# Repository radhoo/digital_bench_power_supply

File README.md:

# digital_bench_power_supply
A new design for a digital bench power supply built using the Atmega8.

(C) 2015 Radu Motisan, http://www.pocketmagic.net/digital-bench-power-supply/
radu.motisan@gmail.com

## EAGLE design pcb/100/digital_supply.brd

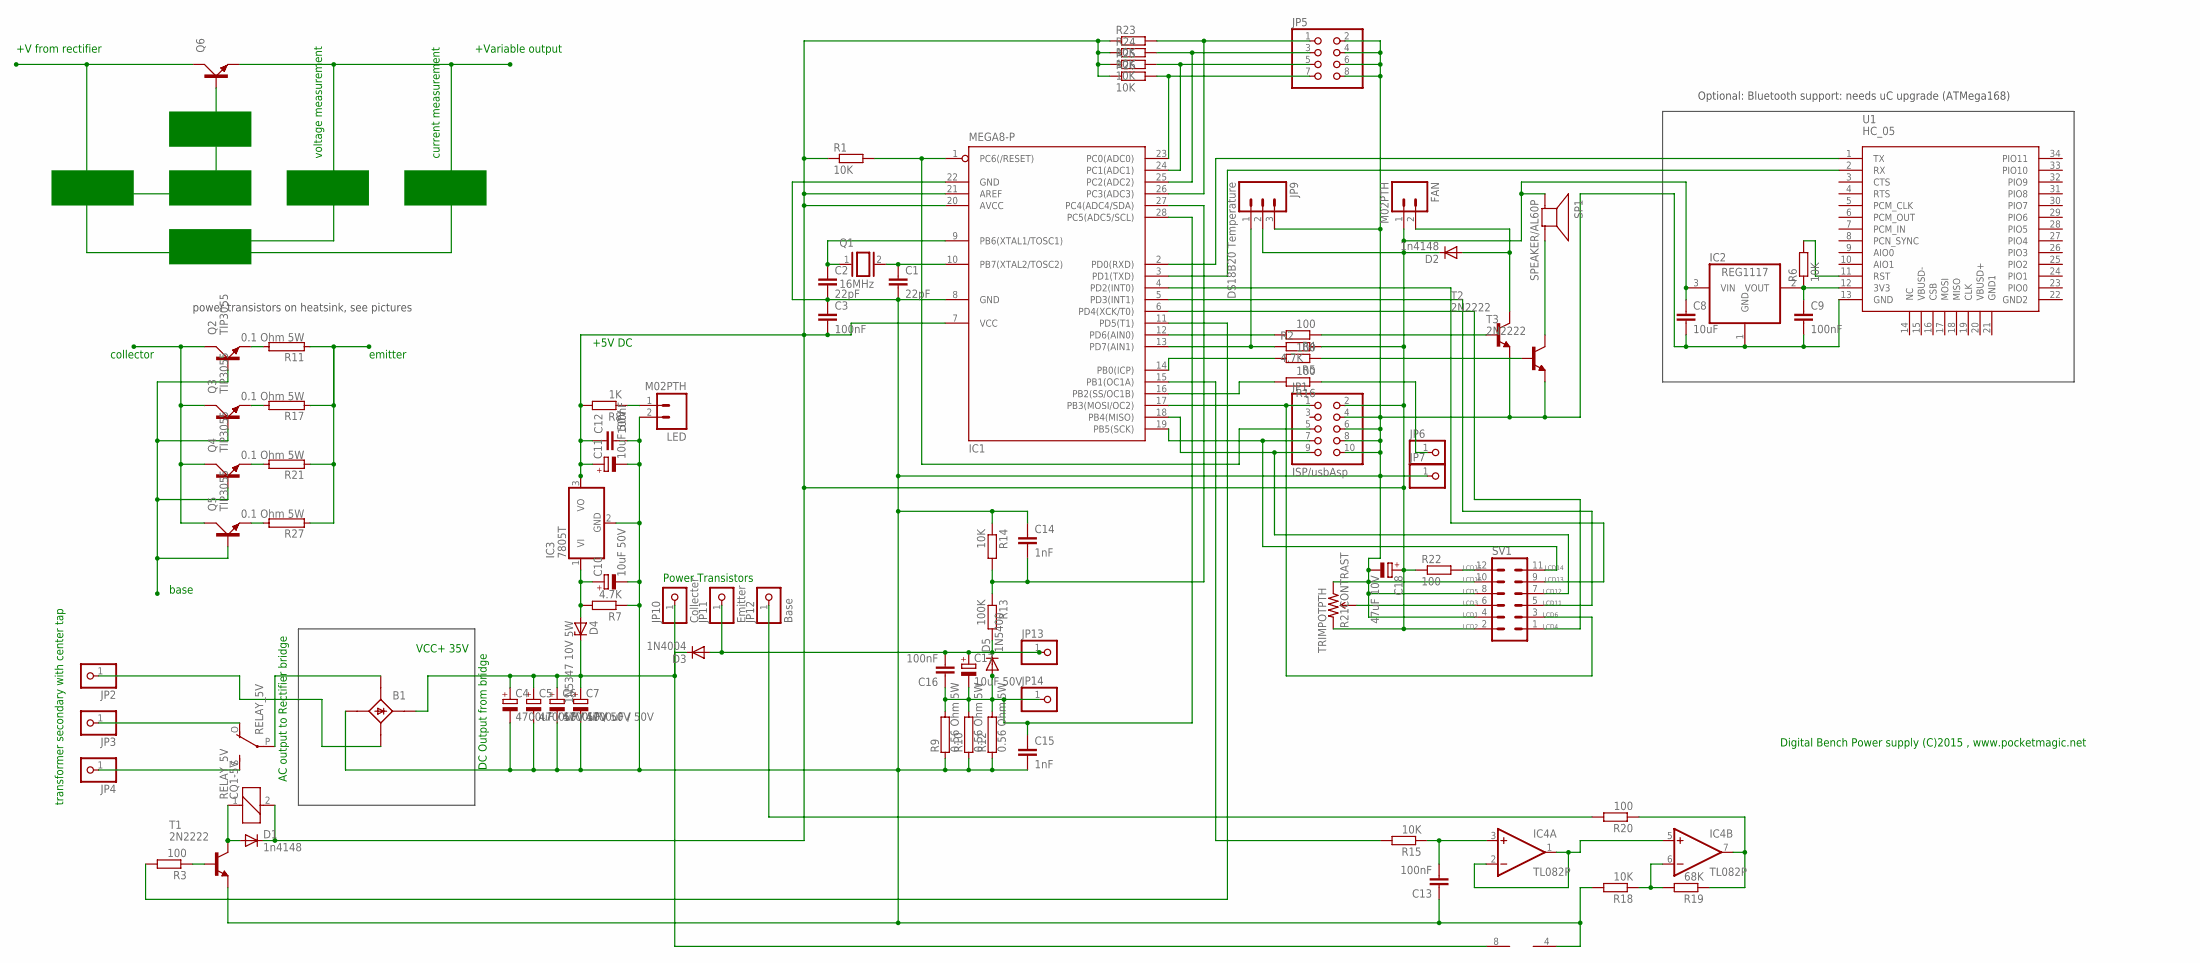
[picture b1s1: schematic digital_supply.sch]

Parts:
B1: B25A-
C1, C2: 22pF; C025-024X044
C3, C12, C13, C16: 100nF; C025-024X044
C4, C5, C6, C7: 4700uF / 50V; E7,5-18
C8: 10uF; C0805
C9: 100nF; C0805
C10, C11, C17: 10uF 50V; E2-5
C14, C15: 1nF; C025-024X044
C18: 47uF 10V; E2-5
D1, D2: 1n4148; D-5
D3: 1N4004; DO41-10
D4: 1N5347 10V 5W; DO34Z7
D5: 1N5400; DO201-15
FAN: M02PTH; 1X02
IC1: MEGA8-P; DIL28-3
IC2: REG1117; SOT223
IC3: 7805T; TO220H
IC4: TL082P; DIL08
JP1: ISP/usbAsp; 2X05
JP2, JP3, JP4, JP6, JP7, JP13, JP14: PINHD-1X1; 1X01
JP5: PINHD-2X4; 2X04
JP9: DS18B20 Temperature; 1X03
JP10: Collecter; 1X01
JP11: Emitter; 1X01
JP12: Base; 1X01
LED: M02PTH; 1X02
Q1: 16MHz; QS
Q2, Q3, Q4, Q5, Q6: TIP3055; TOP3AV
R1, R14, R15, R18, R23, R24, R25, R26: 10K; 0204/7
R2, R7: 4.7K; 0204/7
R3, R4, R5, R16, R20, R22: 100; 0204/7
R6: 10K; M0805
R8: 1K; 0204/7
R9, R10, R12: 0.56 Ohm 5W; AC05
R11, R17, R21, R27: 0.1 Ohm 5W; AC05
R13: 100K; 0204/7
R19: 68K; 0204/7
R21CONTRAST: TRIMPOTPTH; TRIM_POT_PTH
RELAY_5V: CQ1-5V; G5LE
SP1: SPEAKER/AL60P; AL60P
SV1: MA06-2
T1, T2, T3: 2N2222; TO92-EBC-OVAL
U1: HC_05; BLUETOOTH_SMD

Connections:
unnamed: C1.1, IC1.10 (PB7(XTAL2/TOSC2)), Q1.2
unnamed: C2.1, IC1.9 (PB6(XTAL1/TOSC1)), Q1.1
unnamed: B1.-1 (-), C1.2, C2.2, C3.1, C4.-, C5.-, C6.-, C7.-, C8.2, C9.2, C10.-, C11.-, C12.2, C13.1, C14.1, C15.2, C18.-, IC1.8 (GND), IC1.22 (GND), IC2.1 (GND), IC3.2 (GND), IC4.4 (V-), JP1.4, JP1.6, JP1.8, JP1.10, JP5.2, JP5.4, JP5.6, JP5.8, JP7.1, JP9.3, LED.2, R7.1, R9.1, R10.1, R12.1, R14.1, R18.2, R21CONTRAST.1 (CCW), SV1.4, SV1.8, SV1.10, T1.E, T2.E, T3.E, U1.13 (GND)
unnamed: LED.1, R8.1
unnamed: IC1.1 (PC6(/RESET)), JP1.5, R1.2
unnamed: IC1.17 (PB3(MOSI/OC2)), JP1.1, SV1.3
unnamed: IC1.18 (PB4(MISO)), JP1.9, SV1.7
unnamed: IC1.4 (PD2(INT0)), SV1.9
unnamed: IC1.14 (PB0(ICP)), R5.2
unnamed: IC1.13 (PD7(AIN1)), JP9.1, R2.1
unnamed: JP3.1, RELAY_5V.O
unnamed: JP4.1, RELAY_5V.S
unnamed: B1.AC2- (AC2), JP2.1
unnamed: B1.AC1- (AC1), RELAY_5V.P
unnamed: D1.A, RELAY_5V.1, T1.C
unnamed: B1.+1 (+), C4.+, C5.+, C6.+, C7.+, D3.C, D4.C, IC4.8 (V+), JP10.1
unnamed: R3.1, T1.B
unnamed: IC1.11 (PD5(T1)), R3.2
unnamed: IC1.12 (PD6(AIN0)), R4.2
unnamed: C15.1, C16.1, C17.-, D5.A, IC1.28 (PC5(ADC5/SCL)), JP14.1, R9.2, R10.2, R12.2
unnamed: IC1.15 (PB1(OC1A)), R15.2
unnamed: C14.2, IC1.27 (PC4(ADC4/SDA)), R13.1, R14.2
unnamed: R4.1, T2.B
unnamed: D2.A, FAN.2, T2.C
unnamed: IC1.16 (PB2(SS/OC1B)), R16.2
unnamed: R5.1, T3.B
unnamed: SP1.2 (-), T3.C
unnamed: C16.2, C17.+, D3.A, D5.C, JP11.1, JP13.1, R13.2
unnamed: IC1.2 (PD0(RXD)), U1.1 (TX)
unnamed: IC1.3 (PD1(TXD)), U1.2 (RX)
unnamed: C9.1, IC2.2 (VOUT), R6.1, U1.12 (3V3)
unnamed: C10.+, D4.A, IC3.1 (VI), R7.2
unnamed: R6.2, U1.11 (RST)
unnamed: Q2.E, R11.2
unnamed: JP6.1, R16.1
unnamed: C13.2, IC4.3 (+IN), R15.1
unnamed: IC4.1 (OUT), IC4.2 (-IN), IC4.5 (+IN)
unnamed: IC4.6 (-IN), R18.1, R19.2
unnamed: IC4.7 (OUT), R19.1, R20.1
unnamed: JP12.1, R20.2
unnamed: IC1.6 (PD4(XCK/T0)), SV1.1
unnamed: IC1.5 (PD3(INT1)), SV1.5
unnamed: IC1.19 (PB5(SCK)), JP1.7, SV1.11
unnamed: R21CONTRAST.2 (WIPER), SV1.6
unnamed: R22.2, SV1.12
unnamed: C3.2, C8.1, C11.+, C12.1, C18.+, D1.C, D2.C, FAN.1, IC1.7 (VCC), IC1.20 (AVCC), IC1.21 (AREF), IC2.3 (VIN), IC3.3 (VO), JP1.2, JP9.2, R1.1, R2.2, R8.2, R21CONTRAST.3 (CW), R22.1, R23.1, R24.1, R25.1, R26.1, RELAY_5V.2, SP1.1 (+), SV1.2
unnamed: IC1.26 (PC3(ADC3)), JP5.1, R23.2
unnamed: IC1.25 (PC2(ADC2)), JP5.3, R24.2
unnamed: IC1.24 (PC1(ADC1)), JP5.5, R25.2
unnamed: IC1.23 (PC0(ADC0)), JP5.7, R26.2
unnamed: Q3.E, R17.2
unnamed: Q4.E, R21.2
unnamed: Q5.E, R27.2
unnamed: R11.1, R17.1, R21.1, R27.1
unnamed: Q2.C, Q3.C, Q4.C, Q5.C
unnamed: Q2.B, Q3.B, Q4.B, Q5.B

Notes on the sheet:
transformer secondary with center tap
AC output to Rectifier bridge
DC Output from bridge
VCC+ 35V
+5V DC
Power Transistors
Optional: Bluetooth support: needs uC upgrade (ATMega168)
LCD2 LCD4
LCD1 LCD6
LCD3 LCD11
LCD5 LCD12
LCD16 LCD13
LCD15 LCD14
power transistors on heatsink, see pictures
base
emitter
collector
control logic
+V from rectifier
DAC
ADC
AMPLIFIER
atmega8
SHUNT
+Variable output
voltage measurement
current measurement
DIVIDER
Digital Bench Power supply (C)2015 , www.pocketmagic.net

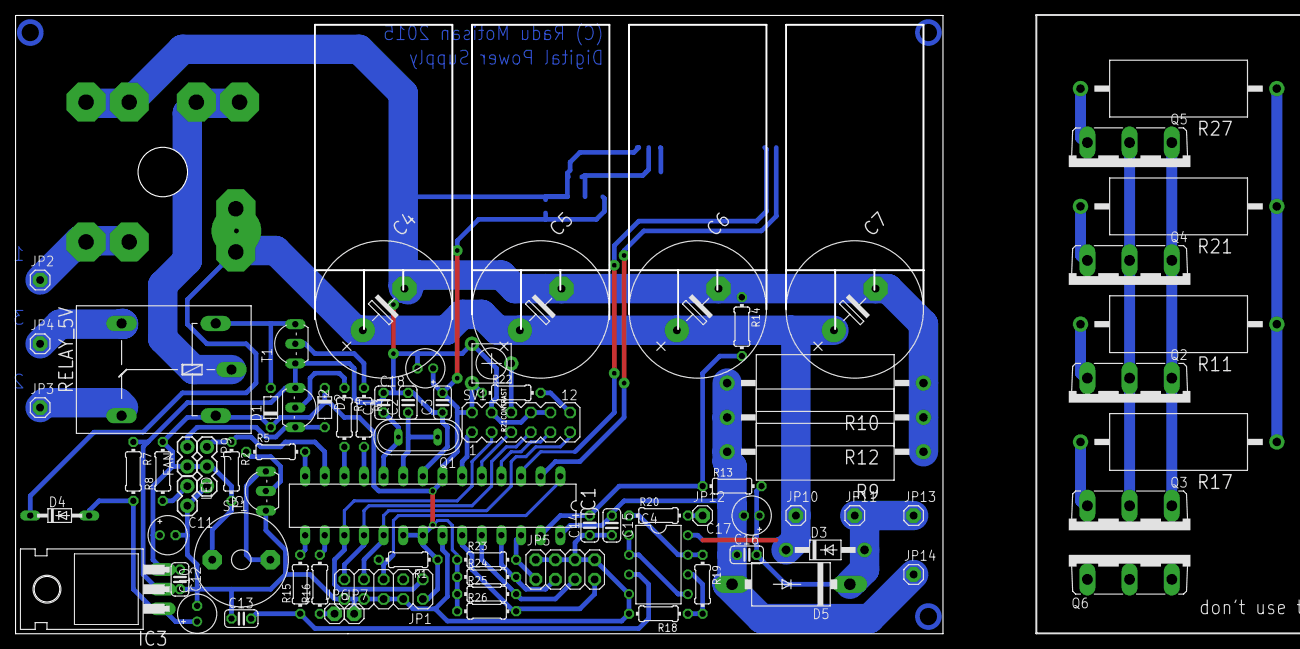
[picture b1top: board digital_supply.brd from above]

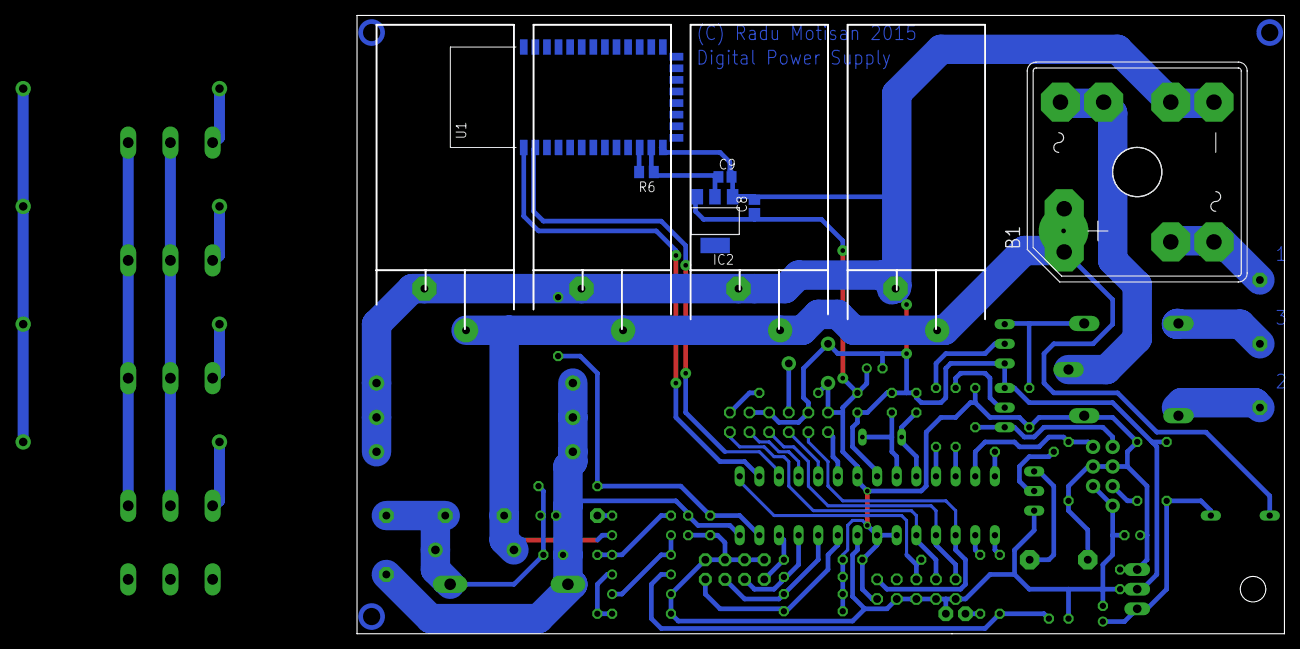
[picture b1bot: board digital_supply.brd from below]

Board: 2 copper layers, 120.0 x 80.0 mm, 84 parts (6 on the bottom side), 56 nets.

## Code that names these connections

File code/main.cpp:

/*
 File:       main.cpp
 Version:    1.0 - first version
 Date:       April 7, 2015
 License:	GPL v2

 Digital Bench Power supply
 http://www.pocketmagic.net/digital-bench-power-supply/

 ****************************************************************************
 Copyright (C) 2015 Radu Motisan  <radu.motisan@gmail.com>

 http://www.pocketmagic.net

 This program is free software; you can redistribute it and/or modify
 it under the terms of the GNU General Public License as published by
 the Free Software Foundation; either version 2 of the License, or
 (at your option) any later version.

 This program is distributed in the hope that it will be useful,
 but WITHOUT ANY WARRANTY; without even the implied warranty of
 MERCHANTABILITY or FITNESS FOR A PARTICULAR PURPOSE.  See the
 GNU General Public License for more details.

 You should have received a copy of the GNU General Public License
 along with this program; if not, write to the Free Software
 Foundation, Inc., 59 Temple Place, Suite 330, Boston, MA  02111-1307  USA
 ****************************************************************************
 */
#include <avr/io.h>
#include <avr/interrupt.h>
#include <avr/wdt.h>
#include <string.h>
#include <stdlib.h>
#include "timeout.h"
#include "io/DigitalIn.h"
#include "io/DigitalOut.h"
#include "sensors/ds18b20.h"
#include "lcd/hd44780.h"
#include "misc/aux.h"
#include "misc/pwm.h"


/************************************************************************************************************************************************/
/* Main entry point                                                    																			*/
/************************************************************************************************************************************************/
HD44780 	lcd;
DS18B20 	ds18b20;
PWM 		pwm;
DigitalOut 	relay,
			speaker,
			fan;
DigitalIn 	but1, // v+
			but2, // v-
			but3, // i+
			but4; // i-
float tempval = 0;
float vref = 5.0;

/* power control modes */
#define MODE_MEASURE_CURRENT 0
#define MODE_MEASURE_VOLTAGE 1
volatile bool adc_mode = MODE_MEASURE_CURRENT;
volatile float current = 0, voltage = 0;

/* my power supply after rectifier shows 16.1V on the center tap and 33.8V on full secondary
 * opamp will introduce some upper voltage limitations. Currently using TL082 and we can reach close to 26V maximum
 */
#define VOLTAGE_LIMIT	26
#define CURRENT_LIMIT	5
#define TEMPERATURE_STARTFAN 50 // if 40degrees celsius are reached, we will start the fan
#define TEMPERATURE_SHUTDOWN 70 // if 80degrees celsius are reached, we will reduce the power until the unit cools down


/* set default values: later save/load them to/from EEPROM */
volatile float targetVol = 5.0, targetCur = 1;

volatile bool alarm = false;
uint16_t cycles = 0;


// Interrupt service routine for the ADC completion
// we measure the current (PC5) and the voltage (PC4) alternatively
ISR(ADC_vect){
	uint16_t analogVal = ADCL | (ADCH << 8);
	if (adc_mode == MODE_MEASURE_CURRENT) {
		current = (analogVal / 1024.0 * vref) / 0.186666; // the output power resistor measures 0.55Ohm
		// alternate mode
		adc_mode = MODE_MEASURE_VOLTAGE;
		ADMUX = PC4; // next time we will do ADC on PC4, to get the voltage
	} else if (adc_mode == MODE_MEASURE_VOLTAGE) {
		// the actual R13 and R14 resistors can be measured using a multimeter for better accuracy
		float R14 = 9.87, /*10k*/ R13 = 98.2; /*100K */
		voltage = analogVal / 1024.0 * (R13 + R14) / R14 * vref;
		// alternate mode
		adc_mode = MODE_MEASURE_CURRENT;
		ADMUX = PC5; // next time we will do ADC on PC5, to get the current
	}

	// If free-running mode is enabled (ADFR), we don't need to restart conversion
	// But we can't use ADFR as we want to monitor two separate ADC channels alternatively

	// start another ADC conversion
	ADCSRA = (1<<ADEN) | (1<<ADIE) | (1<<ADIF) /* | (1<<ADFR) */ | (1<<ADSC) |
				(1<<ADPS2) | (1<<ADPS1) | (1<<ADPS0); // set prescaler to 128 (16M/128=125kHz, above 200KHz 10bit results are not reliable)

	// control operations, in order

	// 1. act on short circuit
	// decrease quickly on current spike
	if (current > targetCur + targetCur / 2) {
		pwm.setDuty(pwm.getDuty() / 2);
		alarm = true; // will sound alarm in main thread
	}
	// 2.act on over current
	// decrease slowly on higher current
	else if (current > targetCur) {
		pwm.setDuty(pwm.getDuty() - 1);
	}
	// 3.act on over temperature
	else if (tempval > TEMPERATURE_SHUTDOWN) {
		pwm.setDuty(pwm.getDuty() - 1);
		alarm = true;
	}
	// 4. act on over voltage
	// take care of voltage with lower priority
	else if (voltage > targetVol) pwm.setDuty(pwm.getDuty() - 1);
	// 5. act on under voltage
	else if (voltage < targetVol) pwm.setDuty(pwm.getDuty() + 1);
}

int main(void) {
	// setup everything
	relay.init(&PORTD, PD5);
	fan.init(&PORTD, PD6);
	speaker.init(&PORTB, PB0);
	pwm.initPWM();

	but1.init(&PORTC, PC0);
	but2.init(&PORTC, PC1);
	but3.init(&PORTC, PC2);
	but4.init(&PORTC, PC3);


	ds18b20.init(&PORTD, PD7);
	lcd.init(&PORTD, PD4, &PORTB, PB3, &PORTD, PD3, &PORTB, PB4, &PORTD, PD2, &PORTB, PB5); //RS, E, D4, D5, D6, D7

	// setup ADC to measure as interrupt: go for current first
	adc_mode = MODE_MEASURE_CURRENT;
	ADMUX = PC5;
	ADCSRA = (1<<ADEN) | (1<<ADIE) | (1<<ADIF) | (1<<ADSC) |
			(1<<ADPS2) | (1<<ADPS1) | (1<<ADPS0); // set prescaler to 128 (16M/128=125kHz, above 200KHz 10bit results are not reliable)
	sei();

	// show welcome screen
	lcd.sendstring("********************\n"\
				   "*Digital Pwr Supply*\n"\
				   "*pocketmagic.net'15*\n"\
				   "********************\n");

	// keep screen then clear
	//_delay_ms(500);

	// main loop
	while (1) {

		// engage relay if we're at 12V or more. use measured voltage or configured voltage?
		relay.set(targetVol > 12);
		// engage fan is temperature is above threshold
		fan.set(tempval > TEMPERATURE_STARTFAN);

		// limit the frequency for some ops including display and temperature reading
		if (cycles == 0) {
			float temp = 0;
			cli();
			if (ds18b20.readTemperature(&temp) == THERM_OK)
				tempval = temp;
			sei();

			lcd.cursorhome();
			lcd.sendstringformat(
				" +SET: %5.2fV %5.2fA\n"\
				"%5.1fC %5.2fV %5.2fA\n"\
				"%s       PWM:%4d\n"
				"2015 pocketmagic.net",
				targetVol, targetCur,
				tempval, voltage, current,
				fan.get()?" +FAN":"     ",
				pwm.getDuty()
			);
		}
		cycles ++;
		if (cycles > 10000) cycles = 0;


		// sound alarm
		if (alarm) {
			speaker.set(1);
			_delay_ms(30);
			speaker.set(0);
			// stop alarm
			alarm = false;
		}

		// act on buttons
		if (but1.get() == 0) {
			if (targetVol < VOLTAGE_LIMIT) targetVol += 0.1;
			cycles = 0; // force lcd refresh
		}
		if (but2.get() == 0) {
			if (targetVol > 0.1) targetVol -= 0.1;
			cycles = 0; // force lcd refresh
		}
		if (but3.get() == 0) {
			if (targetCur < CURRENT_LIMIT) targetCur += 0.1;
			cycles = 0; // force lcd refresh
		}
		if (but4.get() == 0) {
			if (targetCur > 0.1) targetCur -= 0.1;
			cycles = 0; // force lcd refresh
		}



	}

}

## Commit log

2015-04-27 first release

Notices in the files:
parts and their libraries:
sparkfun-connectors: Licensing: CC v3.0 Share-Alike You are welcome to use this library for commercial purposes.
